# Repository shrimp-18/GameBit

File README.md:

# GameBit
GameBit is a custom project made for Hackclub. 
It is a portable Gaming Console (HAT) with a 2 inch LCD Screen, Audio Capabilities, 8 buttons for gameplay and 2 for on/off functionality, powered by a Raspberry Pi Zero 2W.
It is 130 X 44 mm in dimensions. 

I plan to put custom games in it :3
I made GameBit because I've always wanted to build a hardware project on my own and making a gaming console seemed cute. It was a very challenging project for a beginner, but I have learned a lot in the journey of making it. Game consoles are something that exist and I found a couple tutorials here and there but i still had to use a lot of my own brain to make it. But the experience I got from making this one will help me make a project I've been wanting to make since years and the tutorials for which do not exist.
3D View:

The Schematic:

The PCB:

The BOM:

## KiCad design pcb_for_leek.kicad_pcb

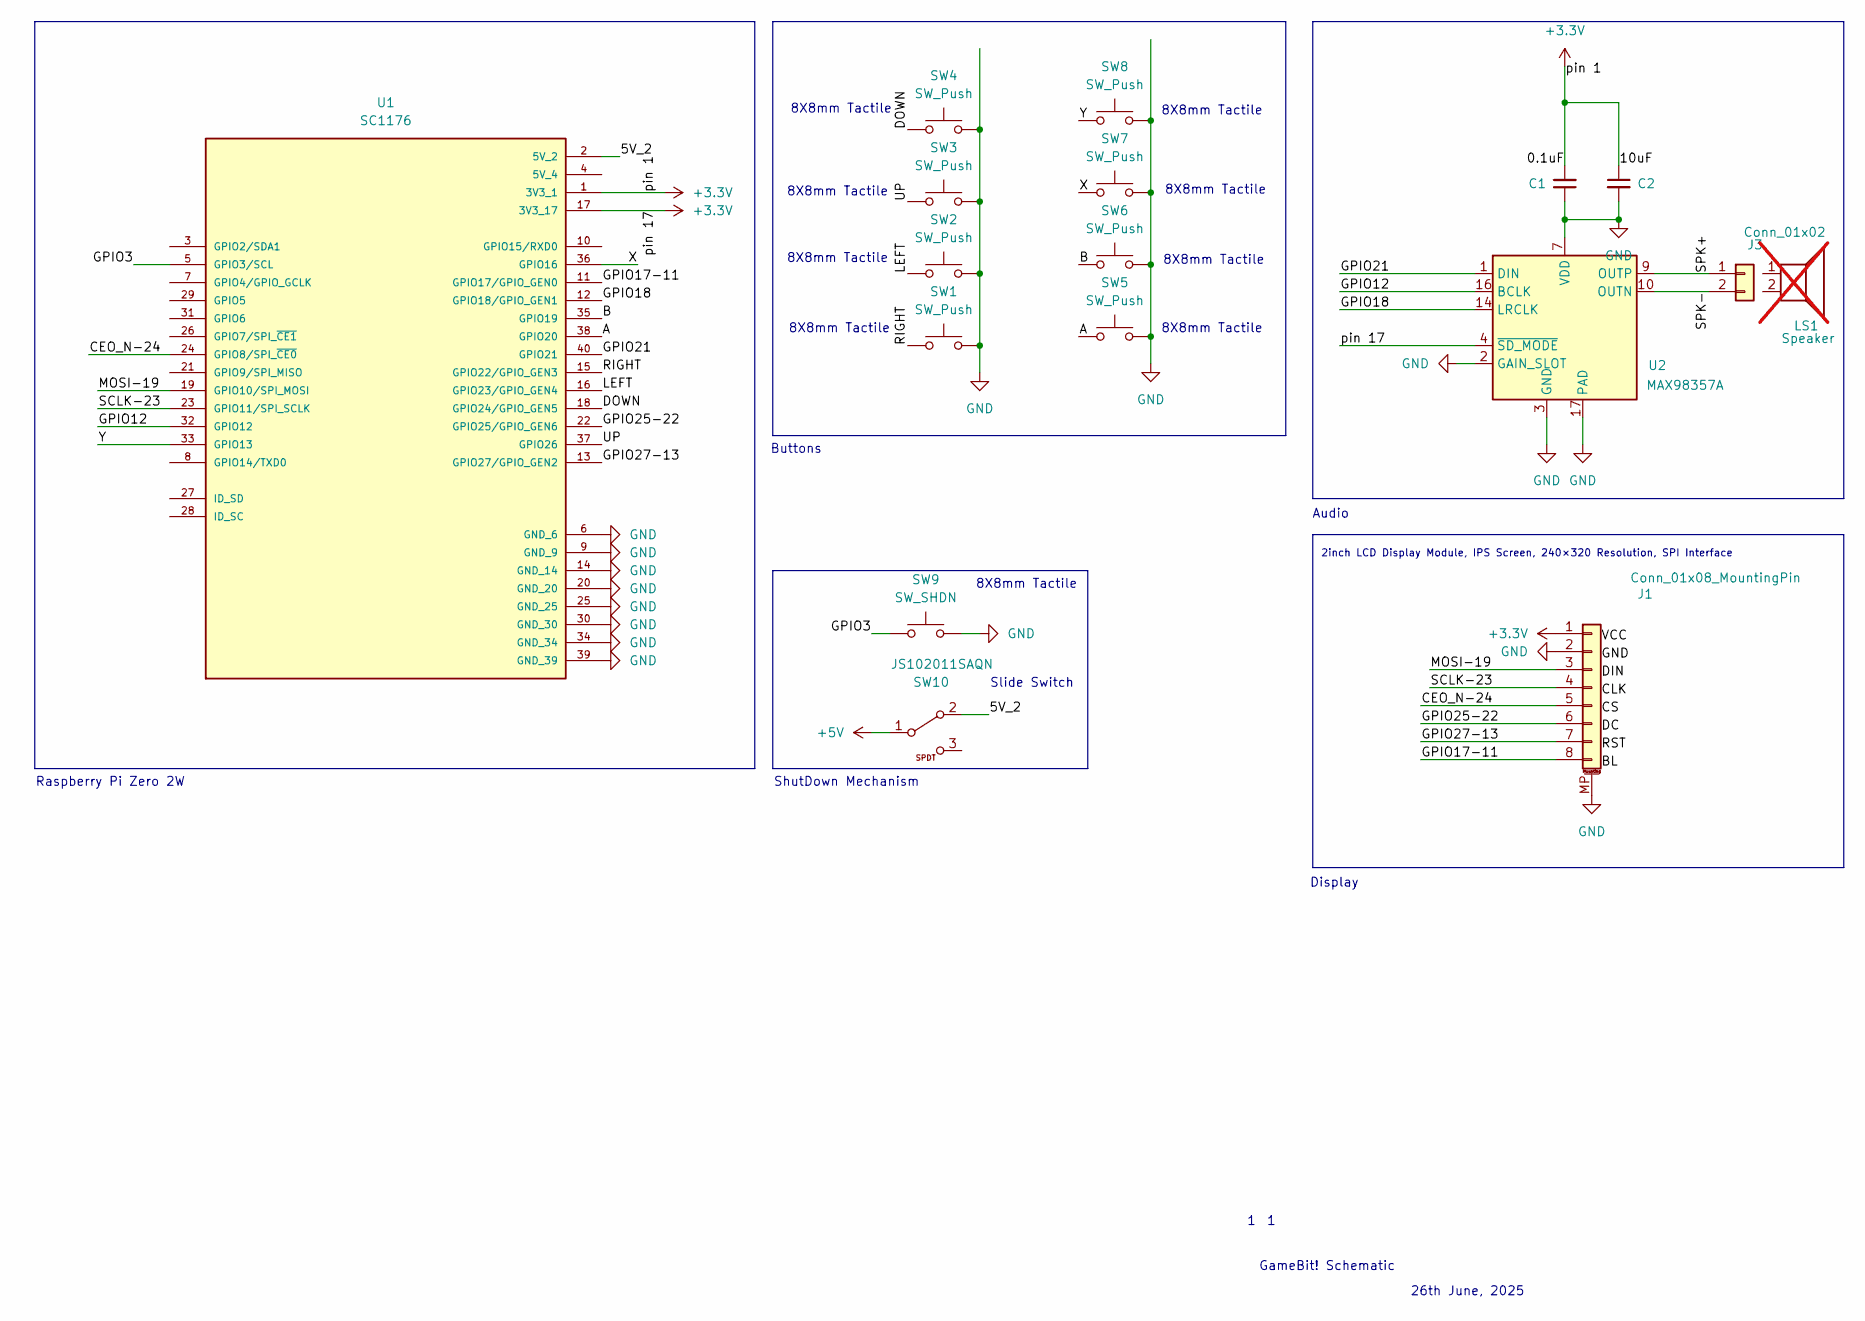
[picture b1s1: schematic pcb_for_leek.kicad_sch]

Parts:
C1: 0.1uF; C_0805
C2: 10uF; C_0805
J1: Conn_01x08_MountingPin; HB_PH3_25418PB2GOP_8Pin
J3: Conn_01x02; PZ254V_11_02P
LS1: Speaker; not fitted
SW1, SW2, SW3, SW4, SW5, SW6, SW7, SW8: SW_Push; TSX08131_3.4x3.0_SMT
SW9: SW_SHDN; TSX08131_3.4x3.0_SMT
SW10: JS102011SAQN; CK_JS102011SAQN; MPN JS102011SAQN; LCSC C221660
U1: SC1176; MODULE_SC1176; PARTREV April 2024; DigiKey_Part_Number 2648-SC1176-ND
U2: MAX98357A; TQFN-16-1EP_3x3mm_P0.5mm_EP1.23x1.23mm

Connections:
+3.3V: C1.2, C2.1, J1.1, U1.1 (3V3_1), U1.17 (3V3_17), U2.4 (~SD_MODE)
+5V: SW10.1 (COM)
/5V_2: SW10.2 (NO), U1.2 (5V_2)
/A: SW5.1, U1.38 (GPIO20)
/B: SW6.1, U1.35 (GPIO19)
/CEO_N-24: J1.5, U1.24 (GPIO8/SPI_~CE0)
/DOWN: SW4.1, U1.18 (GPIO24/GPIO_GEN5)
/GPIO3: SW9.1, U1.5 (GPIO3/SCL)
/GPIO12: U1.32 (GPIO12), U2.16 (BCLK)
/GPIO17-11: J1.8, U1.11 (GPIO17/GPIO_GEN0)
/GPIO18: U1.12 (GPIO18/GPIO_GEN1), U2.14 (LRCLK)
/GPIO21: U1.40 (GPIO21), U2.1 (DIN)
/GPIO25-22: J1.6, U1.22 (GPIO25/GPIO_GEN6)
/GPIO27-13: J1.7, U1.13 (GPIO27/GPIO_GEN2)
/LEFT: SW2.1, U1.16 (GPIO23/GPIO_GEN4)
/MOSI-19: J1.3, U1.19 (GPIO10/SPI_MOSI)
/RIGHT: SW1.1, U1.15 (GPIO22/GPIO_GEN3)
/SCLK-23: J1.4, U1.23 (GPIO11/SPI_SCLK)
/SPK+: J3.1 (SPK+), U2.9 (OUTP)
/SPK-: J3.2 (SPK-), U2.10 (OUTN)
/UP: SW3.1, U1.37 (GPIO26)
/X: SW7.1, U1.36 (GPIO16)
/Y: SW8.1, U1.33 (GPIO13)
GND: C1.1, C2.2, J1.2, J1.MP (MountPin), SW1.2, SW2.2, SW3.2, SW4.2, SW5.2, SW6.2, SW7.2, SW8.2, SW9.2, U1.6 (GND_6), U1.9 (GND_9), U1.14 (GND_14), U1.20 (GND_20), U1.25 (GND_25), U1.30 (GND_30), U1.34 (GND_34), U1.39 (GND_39), U2.2 (GAIN_SLOT), U2.3 (GND), U2.7 (VDD), U2.8 (VDD), U2.11 (GND), U2.15 (GND), U2.17 (PAD)

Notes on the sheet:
8X8mm Tactile
Audio
2inch LCD Display Module, IPS Screen, 240×320 Resolution, SPI Interface
GameBit! Schematic
26th June, 2025
Slide Switch
Raspberry Pi Zero 2W
Display
Buttons
ShutDown Mechanism

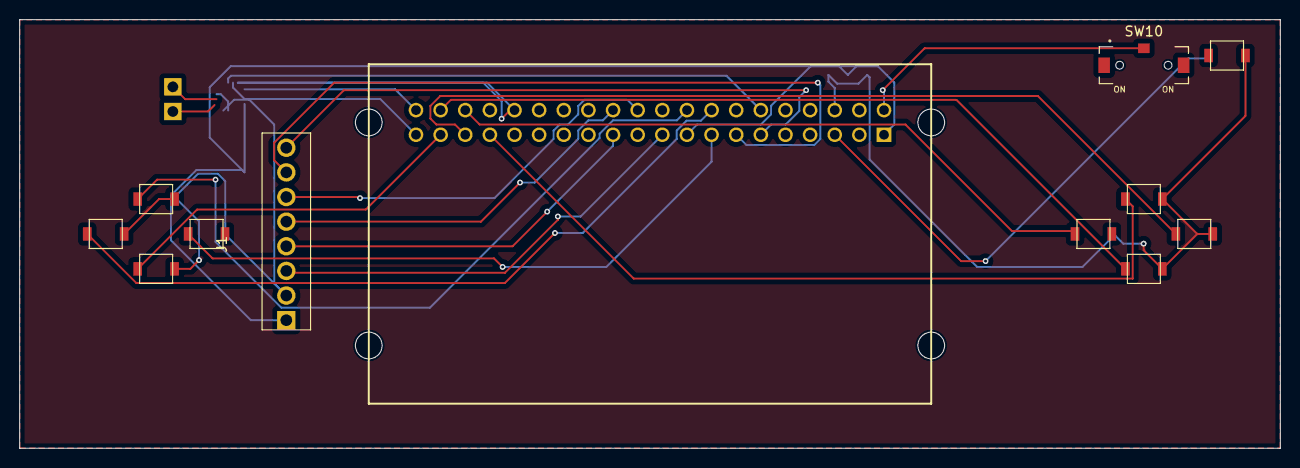
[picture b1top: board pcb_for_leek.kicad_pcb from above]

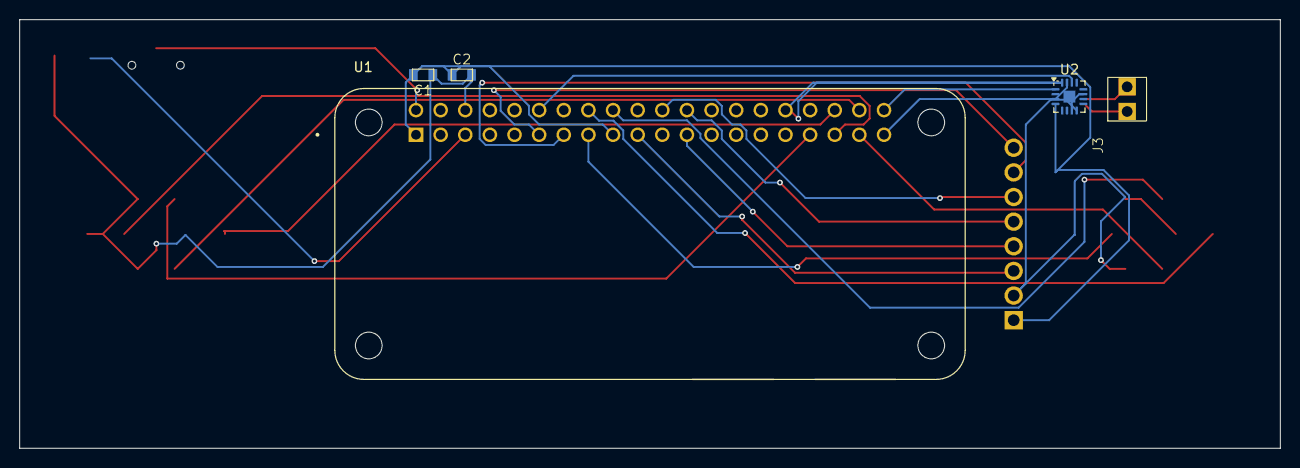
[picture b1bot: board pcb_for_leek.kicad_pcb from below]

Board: 2 copper layers, 130.0 x 44.2 mm, 16 parts (5 on the bottom side), 23 nets.

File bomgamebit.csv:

Reference,Value,Datasheet,Footprint,Qty,DNP,Part
C1,0.1uF,https://lcsc.com/datasheet/lcsc_datasheet_2304140030_TORCH-C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,cap:C_0805,1,,0.1uF Capacitor
C2,10uF,https://lcsc.com/datasheet/lcsc_datasheet_2304140030_Samsung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,cap:C_0805,1,,10uF Capacitor
J1,Conn_01x08_MountingPin,https://lcsc.com/product-detail/image/HB-PH3-25418PB2GOP_C63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,mount:HB_PH3_25418PB2GOP_8Pin,1,,Mounting pin 1x8
J3,Conn_01x02,https://lcsc.com/product-detail/image/PZ254V-11-02P_C492401.html,cap:PZ254V_11_02P,1,,Mounting pin 1x2
LS1,Speaker,https://jlcpcb.com/api/file/downloadByFileSystemAccessId/859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,,1,DNP,Speaker 8ohm 
"SW1,SW2,SW3,SW4,SW5,SW6,SW7,SW8",SW_Push,https://www.khon-switch.com/upload/1c/202404/TSW08131.pdf,button8:TSX08131_3.4x3.0_SMT,8,,8X8 tactile push button
SW9,SW_SHDN,https://www.khon-switch.com/upload/1c/202404/TSW08131.pdf,on/off:TSX08131_3.4x3.0_SMT,1,,8X8 tactile push button
SW10,JS102011SAQN,https://lcsc.com/datasheet/lcsc_datasheet_2410010333_C-K-JS1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,on/off:CK_JS102011SAQN,1,,Slide button
U1,SC1176,https://datasheets.raspberrypi.com/rpizero2/raspberry-pi-zer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,rpi:MODULE_SC1176,1,,Raspberry Pi Zero 2W
U2,MAX98357A,https://www.analog.com/media/en/technical-documentation/data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,Package_DFN_QFN:TQFN-16-1EP_3x3mm_P0.5mm_EP1.23x1.23mm,1,,Audio Module 
LCD,,https://files.waveshare.com/upload/a/ad/ST7789VW.pdf,,1,DNP,LCD Display

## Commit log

2025-06-25 Create JOURNAL.md
    Made journal for highway
2025-06-27 Added kicad files
2025-07-06 Added BOM
2025-07-06 routed pcb
2025-07-26 changed the pcb bcs the design was kinda wrong
